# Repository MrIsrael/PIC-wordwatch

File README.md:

# WordWatch with PIC 16F886 (spanish)
- **This project contains all designs, files and code to build a DIY LED watch, wall mountable, which displays the time with letters, in spanish.**<br />
Resolution: 5 minutes. The words change each 5 minutes.<br />
You can find an example of how it looks when finished, opening image "Wordwatch finished.jpg".<br />
Entire design was built around PIC 16F886 from Microchip.<br />
Schematic and PCB design made using Autodesk EAGLE 8.0.1.<br />
Assembler code edited and compiled using Microchip MPLAB IDE v8.92.<br />
PICkit 2 was used for .hex transfer to microcontroller.<br />

## Instructions
--> Check the components listed in .sch file.<br />
--> Build the PCB using the PDF prints. There is a great guide to do it yourself, [here] (https://www.youtube.com/watch?v=lvNCKwAcg90).<br />
--> Burn the .hex to PIC 16F886, using a PICkit 2 or compatible PIC programmer.<br />
--> Use the "front layout" images to print a scale screen for the leds. I suggest create a wood screen, etching the letters with laser cutter.<br />
--> Use any AC/DC adaptor to power the clock. Minimum output voltage - current required: 6V DC, 300 mA.<br />

## How to set time
--> Once powered on, press the button to enter set mode. Words will start to blink.<br />
--> Press button again to change and set hours.<br />
--> Wait 10 seconds without pressing the button. Now minutes start to blink.<br />
--> Press button to change and set minutes.<br />
--> Wait another 10 seconds without pressing the button. Program will return to normal mode.<br />

## Maintainer
- [Israel Uribe](https://github.com/MrIsrael)

## License
MIT © [WordWatch](https://github.com/MrIsrael/PIC-wordwatch)

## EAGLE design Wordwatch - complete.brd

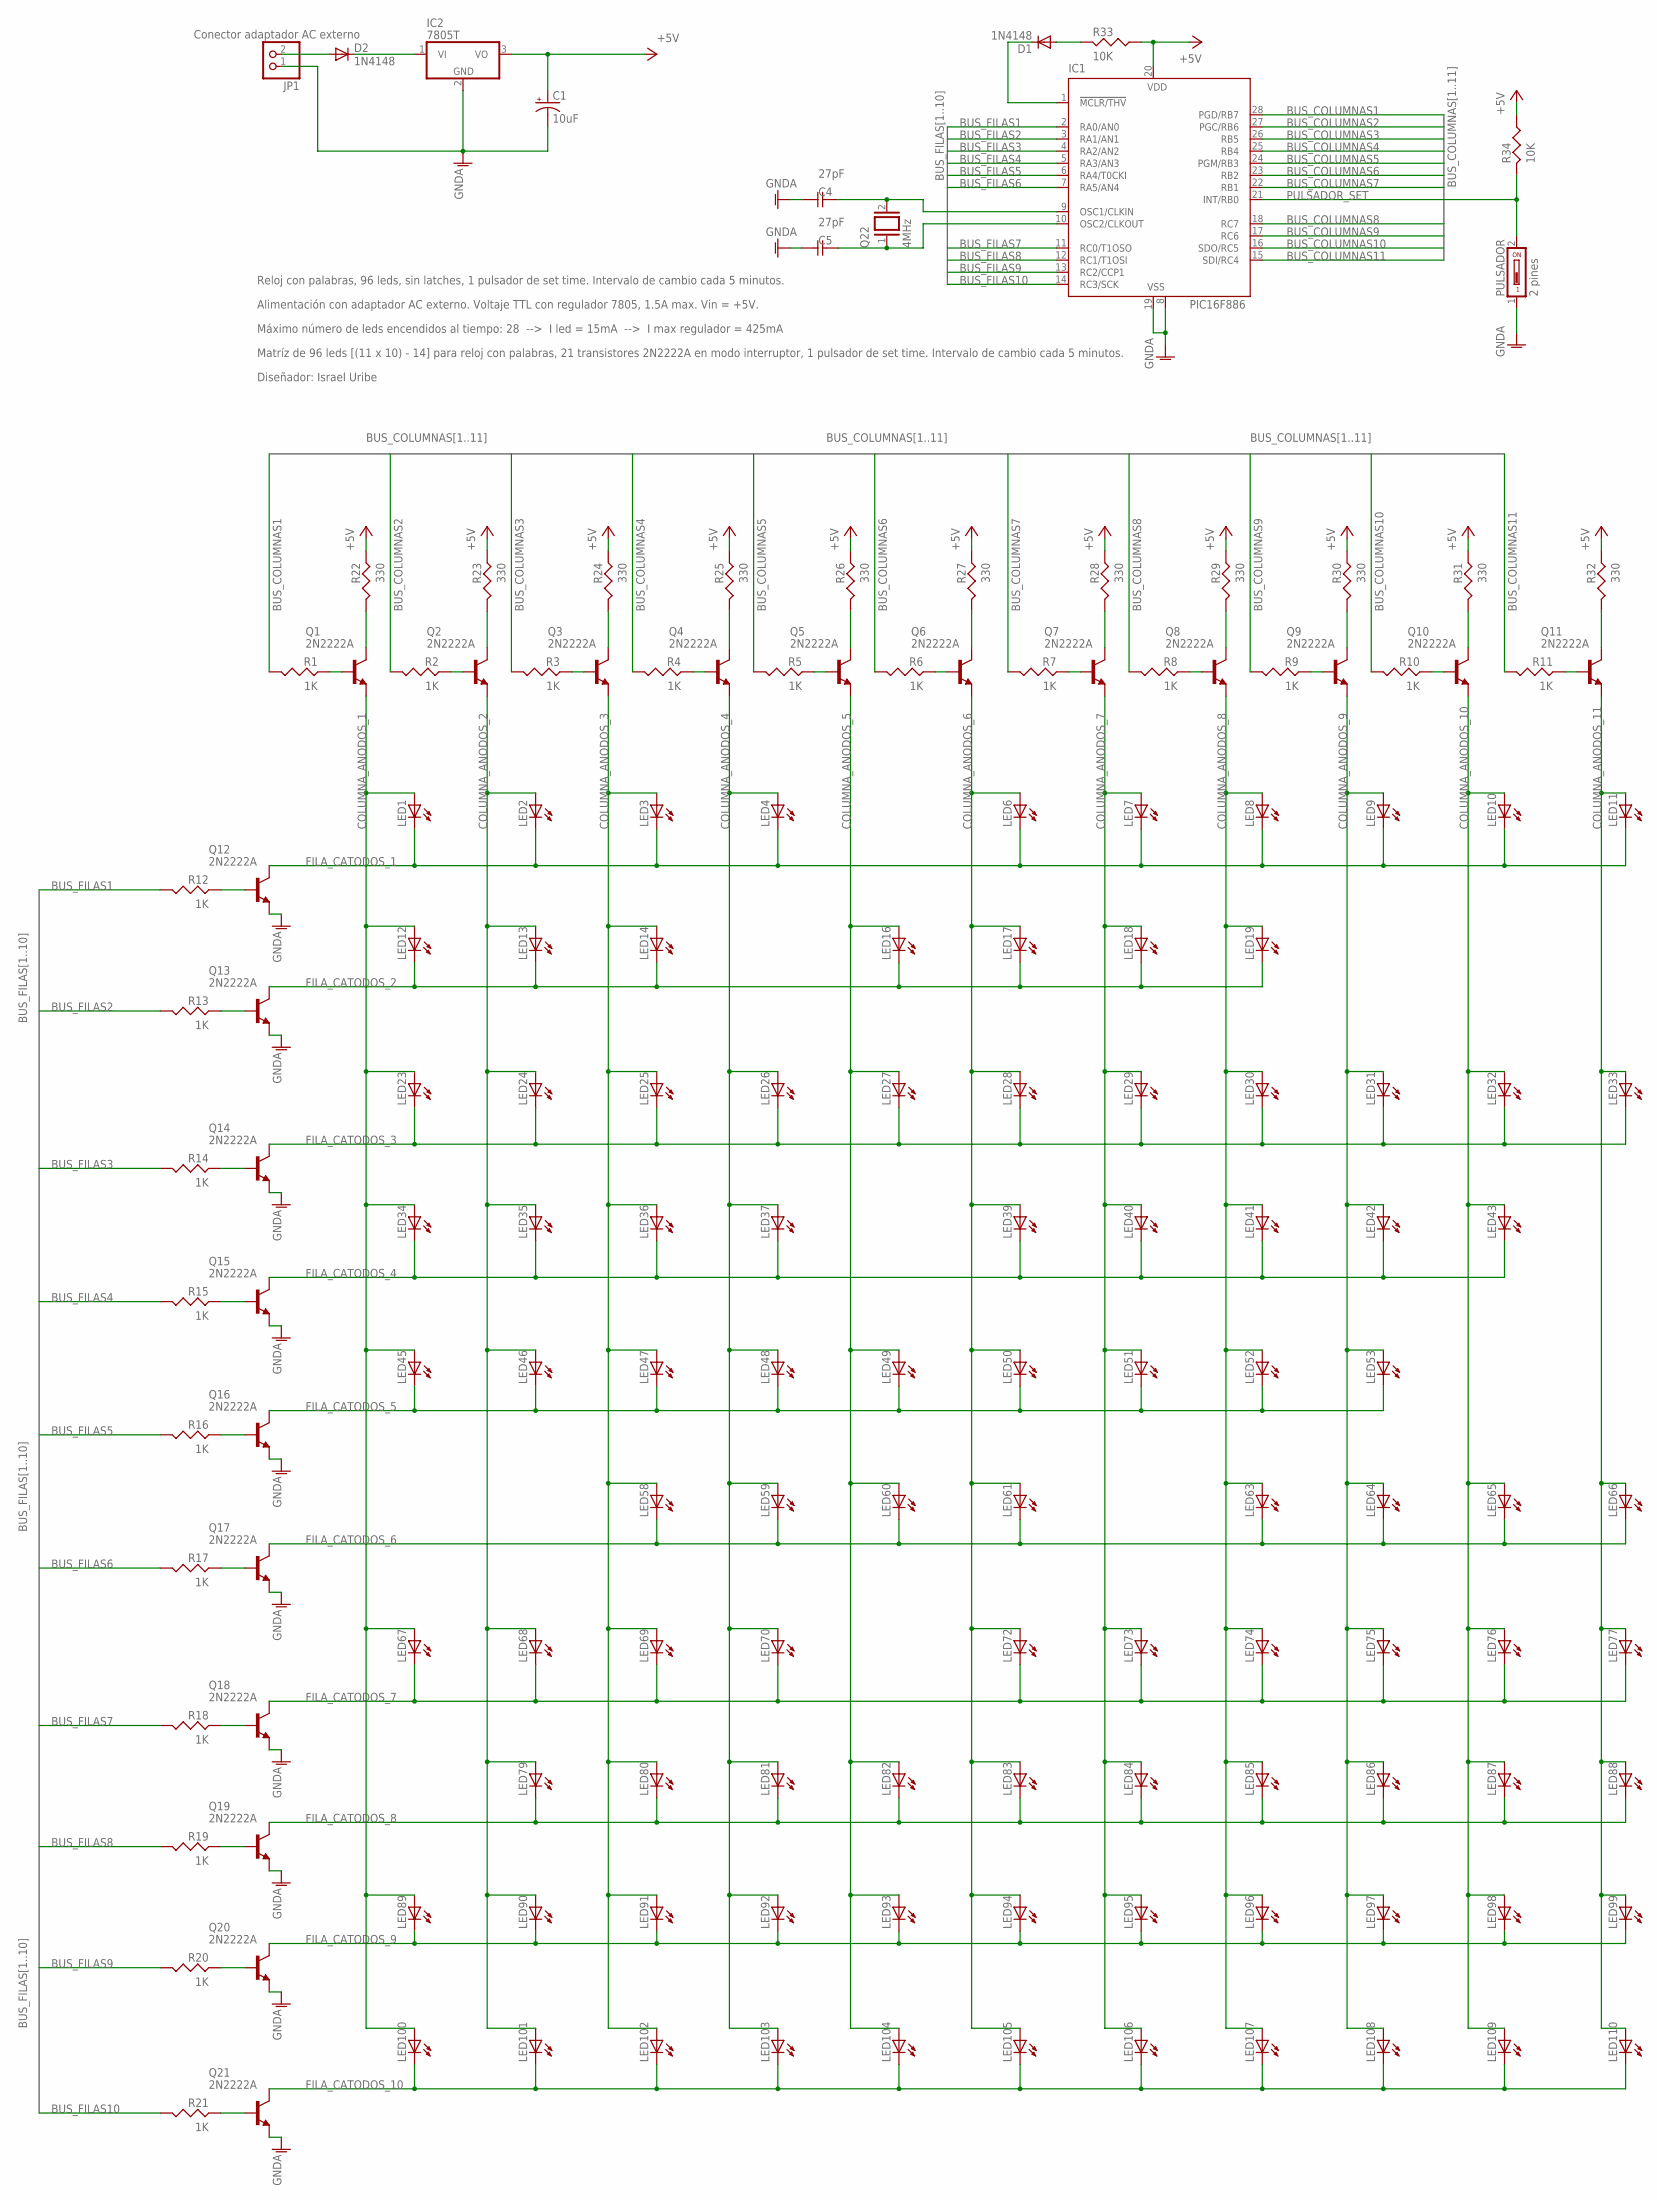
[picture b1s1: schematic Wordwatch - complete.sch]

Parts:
C1: 10uF; E2-4
C4, C5: 27pF; C-2,5
D1, D2: 1N4148; D-7.5
IC1: PIC16F886; DIL28-3
IC2: 7805T; TO220H
JP1: Conector adaptador AC externo; 1X02
LED1, LED2, LED3, LED4, LED6, LED7, LED8, LED9, LED10, LED11, LED12, LED13, LED14, LED16, LED17, LED18, LED19, LED23, LED24, LED25, LED26, LED27, LED28, LED29, LED30, LED31, LED32, LED33, LED34, LED35, LED36, LED37, LED39, LED40, LED41, LED42, LED43, LED45, LED46, LED47, LED48, LED49, LED50, LED51, LED52, LED53, LED58, LED59, LED60, LED61, LED63, LED64, LED65, LED66, LED67, LED68, LED69, LED70, LED72, LED73, LED74, LED75, LED76, LED77, LED79, LED80, LED81, LED82, LED83, LED84, LED85, LED86, LED87, LED88, LED89, LED90, LED91, LED92, LED93, LED94, LED95, LED96, LED97, LED98, LED99, LED100, LED101, LED102, LED103, LED104, LED105, LED106, LED107, LED108, LED109, LED110: LED3MM
PULSADOR: 2 pines; DS-01
Q1, Q2, Q3, Q4, Q5, Q6, Q7, Q8, Q9, Q10, Q11, Q12, Q13, Q14, Q15, Q16, Q17, Q18, Q19, Q20, Q21: 2N2222A; TO92-CBE
Q22: 4MHz; QS
R1, R2, R3, R4, R5, R6, R7, R8, R9, R10, R11, R12, R13, R14, R15, R16, R17, R18, R19, R20, R21: 1K; R-5
R22, R23, R24, R25, R26, R27, R28, R29, R30, R31, R32: 330; R-5
R33, R34: 10K; R-5

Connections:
+5V: C1.+, IC1.20 (VDD), IC2.3 (VO), R22.2, R23.2, R24.2, R25.2, R26.2, R27.2, R28.2, R29.2, R30.2, R31.2, R32.2, R33.1, R34.1
BUS_COLUMNAS1: IC1.28 (PGD/RB7), R1.1
BUS_COLUMNAS2: IC1.27 (PGC/RB6), R2.1
BUS_COLUMNAS3: IC1.26 (RB5), R3.1
BUS_COLUMNAS4: IC1.25 (RB4), R4.1
BUS_COLUMNAS5: IC1.24 (PGM/RB3), R5.1
BUS_COLUMNAS6: IC1.23 (RB2), R6.1
BUS_COLUMNAS7: IC1.22 (RB1), R7.1
BUS_COLUMNAS8: IC1.18 (RC7), R8.1
BUS_COLUMNAS9: IC1.17 (RC6), R9.1
BUS_COLUMNAS10: IC1.16 (SDO/RC5), R10.1
BUS_COLUMNAS11: IC1.15 (SDI/RC4), R11.1
BUS_FILAS1: IC1.2 (RA0/AN0), R12.1
BUS_FILAS2: IC1.3 (RA1/AN1), R13.1
BUS_FILAS3: IC1.4 (RA2/AN2), R14.1
BUS_FILAS4: IC1.5 (RA3/AN3), R15.1
BUS_FILAS5: IC1.6 (RA4/T0CKI), R16.1
BUS_FILAS6: IC1.7 (RA5/AN4), R17.1
BUS_FILAS7: IC1.11 (RC0/T1OSO), R18.1
BUS_FILAS8: IC1.12 (RC1/T1OSI), R19.1
BUS_FILAS9: IC1.13 (RC2/CCP1), R20.1
BUS_FILAS10: IC1.14 (RC3/SCK), R21.1
COLUMNA_ANODOS_1: LED1.A, LED12.A, LED23.A, LED34.A, LED45.A, LED67.A, LED89.A, LED100.A, Q1.E
COLUMNA_ANODOS_2: LED2.A, LED13.A, LED24.A, LED35.A, LED46.A, LED68.A, LED79.A, LED90.A, LED101.A, Q2.E
COLUMNA_ANODOS_3: LED3.A, LED14.A, LED25.A, LED36.A, LED47.A, LED58.A, LED69.A, LED80.A, LED91.A, LED102.A, Q3.E
COLUMNA_ANODOS_4: LED4.A, LED26.A, LED37.A, LED48.A, LED59.A, LED70.A, LED81.A, LED92.A, LED103.A, Q4.E
COLUMNA_ANODOS_5: LED16.A, LED27.A, LED49.A, LED60.A, LED82.A, LED93.A, LED104.A, Q5.E
COLUMNA_ANODOS_6: LED6.A, LED17.A, LED28.A, LED39.A, LED50.A, LED61.A, LED72.A, LED83.A, LED94.A, LED105.A, Q6.E
COLUMNA_ANODOS_7: LED7.A, LED18.A, LED29.A, LED40.A, LED51.A, LED73.A, LED84.A, LED95.A, LED106.A, Q7.E
COLUMNA_ANODOS_8: LED8.A, LED19.A, LED30.A, LED41.A, LED52.A, LED63.A, LED74.A, LED85.A, LED96.A, LED107.A, Q8.E
COLUMNA_ANODOS_9: LED9.A, LED31.A, LED42.A, LED53.A, LED64.A, LED75.A, LED86.A, LED97.A, LED108.A, Q9.E
COLUMNA_ANODOS_10: LED10.A, LED32.A, LED43.A, LED65.A, LED76.A, LED87.A, LED98.A, LED109.A, Q10.E
COLUMNA_ANODOS_11: LED11.A, LED33.A, LED66.A, LED77.A, LED88.A, LED99.A, LED110.A, Q11.E
FILA_CATODOS_1: LED1.K (C), LED2.K (C), LED3.K (C), LED4.K (C), LED6.K (C), LED7.K (C), LED8.K (C), LED9.K (C), LED10.K (C), LED11.K (C), Q12.C
FILA_CATODOS_2: LED12.K (C), LED13.K (C), LED14.K (C), LED16.K (C), LED17.K (C), LED18.K (C), LED19.K (C), Q13.C
FILA_CATODOS_3: LED23.K (C), LED24.K (C), LED25.K (C), LED26.K (C), LED27.K (C), LED28.K (C), LED29.K (C), LED30.K (C), LED31.K (C), LED32.K (C), LED33.K (C), Q14.C
FILA_CATODOS_4: LED34.K (C), LED35.K (C), LED36.K (C), LED37.K (C), LED39.K (C), LED40.K (C), LED41.K (C), LED42.K (C), LED43.K (C), Q15.C
FILA_CATODOS_5: LED45.K (C), LED46.K (C), LED47.K (C), LED48.K (C), LED49.K (C), LED50.K (C), LED51.K (C), LED52.K (C), LED53.K (C), Q16.C
FILA_CATODOS_6: LED58.K (C), LED59.K (C), LED60.K (C), LED61.K (C), LED63.K (C), LED64.K (C), LED65.K (C), LED66.K (C), Q17.C
FILA_CATODOS_7: LED67.K (C), LED68.K (C), LED69.K (C), LED70.K (C), LED72.K (C), LED73.K (C), LED74.K (C), LED75.K (C), LED76.K (C), LED77.K (C), Q18.C
FILA_CATODOS_8: LED79.K (C), LED80.K (C), LED81.K (C), LED82.K (C), LED83.K (C), LED84.K (C), LED85.K (C), LED86.K (C), LED87.K (C), LED88.K (C), Q19.C
FILA_CATODOS_9: LED89.K (C), LED90.K (C), LED91.K (C), LED92.K (C), LED93.K (C), LED94.K (C), LED95.K (C), LED96.K (C), LED97.K (C), LED98.K (C), LED99.K (C), Q20.C
FILA_CATODOS_10: LED100.K (C), LED101.K (C), LED102.K (C), LED103.K (C), LED104.K (C), LED105.K (C), LED106.K (C), LED107.K (C), LED108.K (C), LED109.K (C), LED110.K (C), Q21.C
GNDA: C1.-, C4.2, C5.2, IC1.8 (VSS), IC1.19 (VSS), IC2.2 (GND), JP1.1, PULSADOR.1, Q12.E, Q13.E, Q14.E, Q15.E, Q16.E, Q17.E, Q18.E, Q19.E, Q20.E, Q21.E
unnamed: Q11.C, R32.1
unnamed: Q10.C, R31.1
unnamed: Q9.C, R30.1
unnamed: Q8.C, R29.1
unnamed: Q7.C, R28.1
unnamed: Q6.C, R27.1
unnamed: Q5.C, R26.1
unnamed: Q4.C, R25.1
unnamed: Q3.C, R24.1
unnamed: Q2.C, R23.1
unnamed: Q1.C, R22.1
unnamed: Q1.B, R1.2
unnamed: Q2.B, R2.2
unnamed: Q3.B, R3.2
unnamed: Q4.B, R4.2
unnamed: Q5.B, R5.2
unnamed: Q6.B, R6.2
unnamed: Q7.B, R7.2
unnamed: Q8.B, R8.2
unnamed: Q9.B, R9.2
unnamed: Q10.B, R10.2
unnamed: Q11.B, R11.2
unnamed: Q12.B, R12.2
unnamed: Q13.B, R13.2
unnamed: Q14.B, R14.2
unnamed: Q15.B, R15.2
unnamed: Q16.B, R16.2
unnamed: Q17.B, R17.2
unnamed: Q18.B, R18.2
unnamed: Q19.B, R19.2
unnamed: Q20.B, R20.2
unnamed: Q21.B, R21.2
unnamed: C4.1, IC1.9 (OSC1/CLKIN), Q22.2
unnamed: D1.A, R33.2
unnamed: C5.1, IC1.10 (OSC2/CLKOUT), Q22.1
unnamed: D1.C, IC1.1 (!MCLR/THV)
unnamed: D2.A, JP1.2
unnamed: D2.C, IC2.1 (VI)
PULSADOR_SET: IC1.21 (INT/RB0), PULSADOR.2, R34.2

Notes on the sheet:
Matríz de 96 leds [(11 x 10) - 14] para reloj con palabras, 21 transistores 2N2222A en modo interruptor, 1 pulsador de set time. Intervalo de cambio cada 5 minutos.
Diseñador: Israel Uribe
Reloj con palabras, 96 leds, sin latches, 1 pulsador de set time. Intervalo de cambio cada 5 minutos.
Alimentación con adaptador AC externo. Voltaje TTL con regulador 7805, 1.5A max. Vin = +5V.
Máximo número de leds encendidos al tiempo: 28 --> I led = 15mA --> I max regulador = 425mA

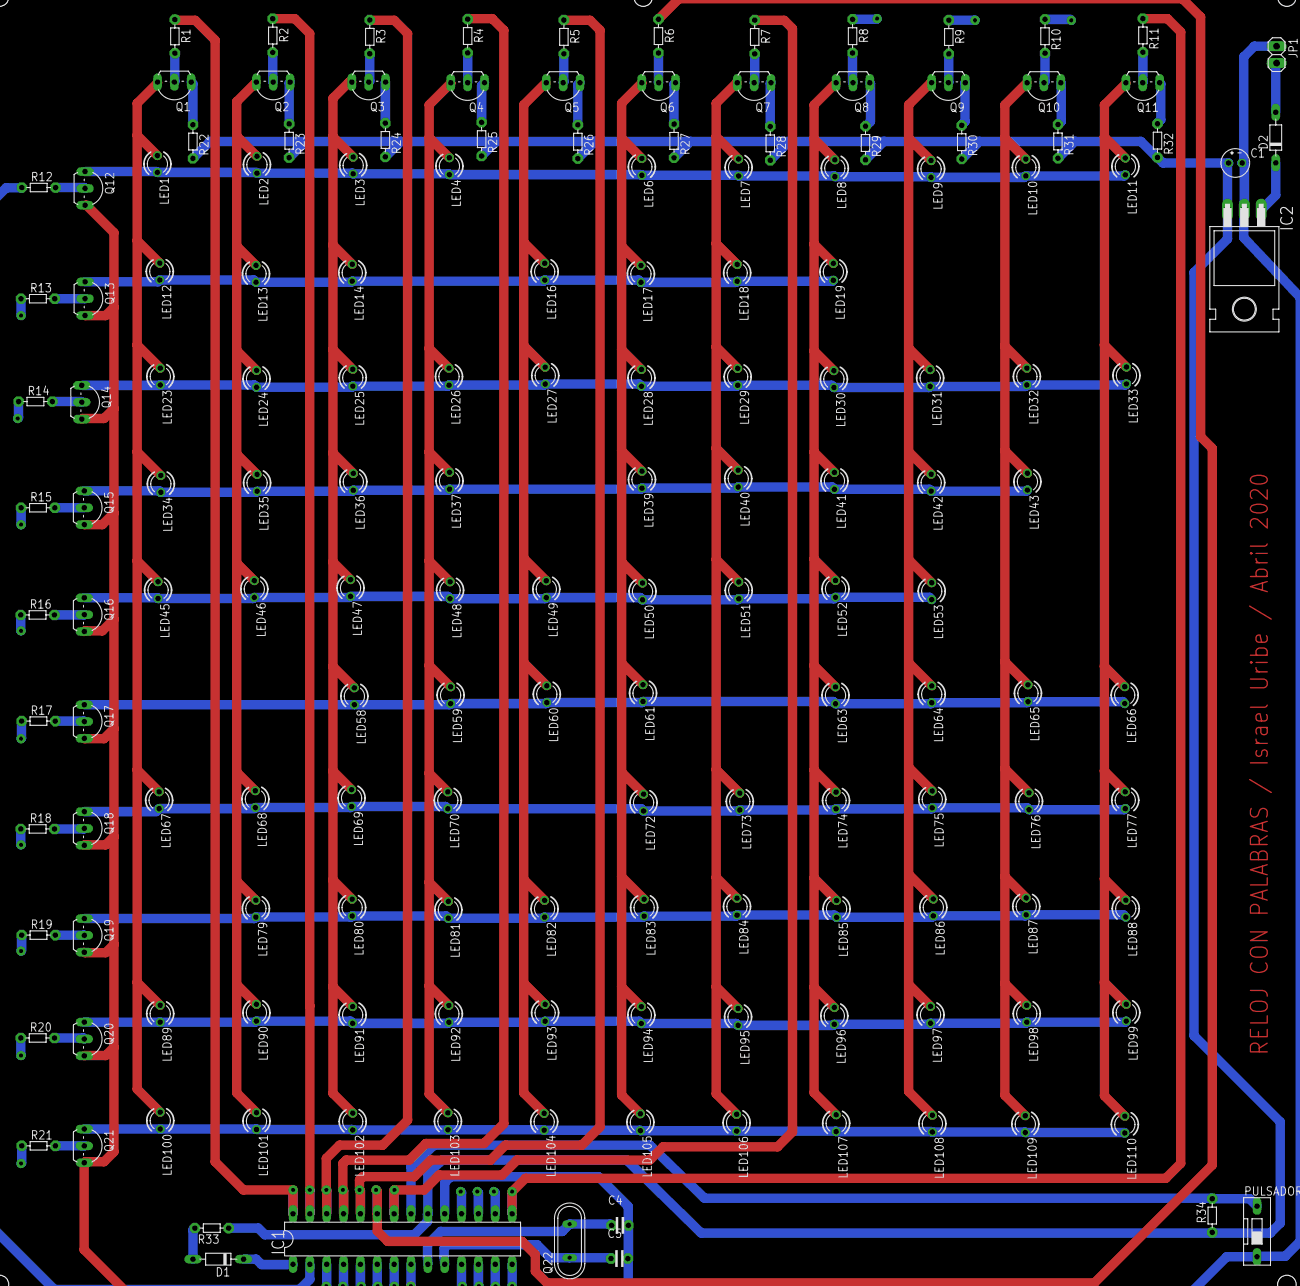
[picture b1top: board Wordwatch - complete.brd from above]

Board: 2 copper layers, 161 parts (0 on the bottom side), 83 nets.

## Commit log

2020-07-05 Final design uploaded to public repository
2020-07-05 Readme added
